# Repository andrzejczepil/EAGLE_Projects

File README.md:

# EAGLE_Projects
Schematics, footprints&amp;Boards

Projekt_KWP - a small project in collab with Agnieszka Zwolińska (UoT Gdańsk), project of working two-tone generator

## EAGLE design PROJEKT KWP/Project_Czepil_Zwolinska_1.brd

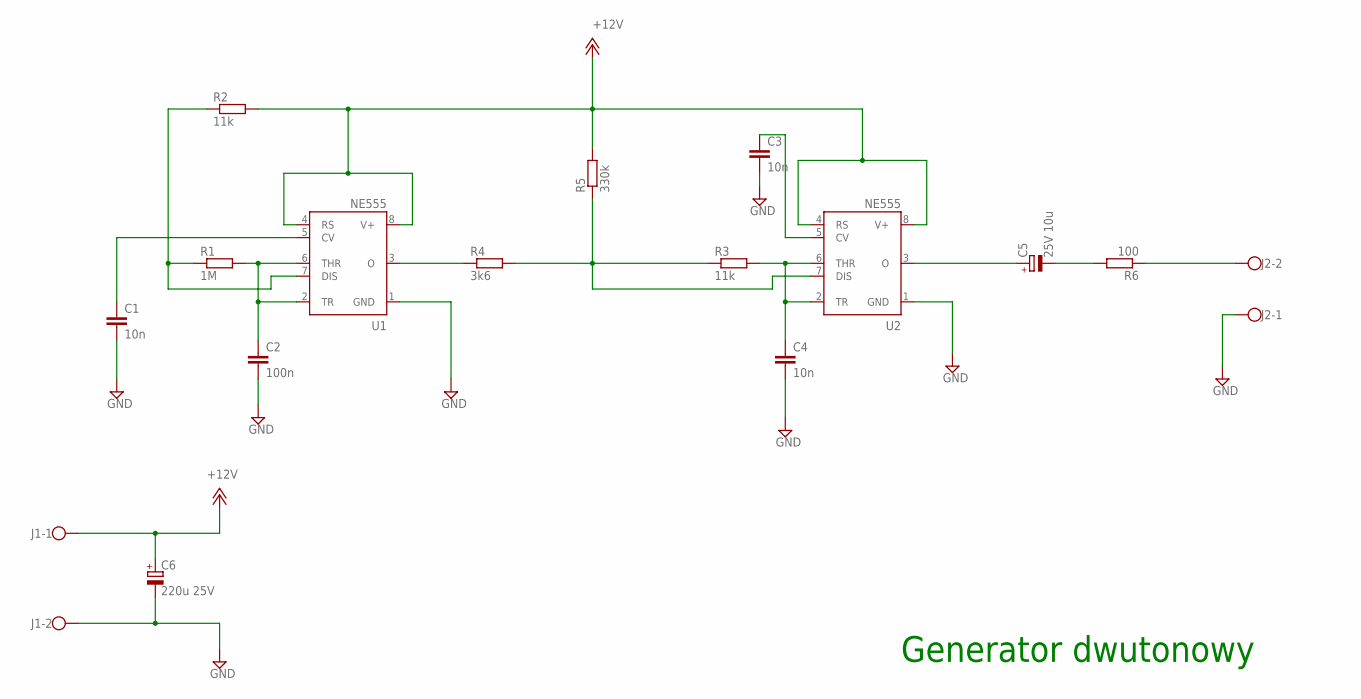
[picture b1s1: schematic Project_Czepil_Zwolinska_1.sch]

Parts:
C1, C3, C4: 10n; C1206
C2: 100n; C1206
C5: 25V 10u; E1,8-4
C6: 220u 25V; E2-4
J1, J2: W237-102
R1: 1M; 0207/10
R2, R3: 11k; 0207/10
R4: 3k6; 0207/10
R5: 330k; 0207/10
R6: 100; 0207/10
U1, U2: NE555; DIL-08

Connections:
+12V: C6.+, J1.1, R2.2, R5.2, U1.4 (RS), U1.8 (V+), U2.4 (RS), U2.8 (V+)
GND: C1.2, C2.2, C3.2, C4.2, C6.-, J1.2, J2.1, U1.1 (GND), U2.1 (GND)
unnamed: J2.2, R6.1
unnamed: C5.-, R6.2
unnamed: R3.1, R4.2, R5.1, U2.7 (DIS)
unnamed: C1.1, U1.5 (CV)
unnamed: R1.1, R2.1, U1.7 (DIS)
unnamed: C2.1, R1.2, U1.2 (TR), U1.6 (THR)
unnamed: C3.1, U2.5 (CV)
unnamed: C5.+, U2.3 (O)
unnamed: C4.1, R3.2, U2.2 (TR), U2.6 (THR)
unnamed: R4.1, U1.3 (O)

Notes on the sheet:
Generator dwutonowy

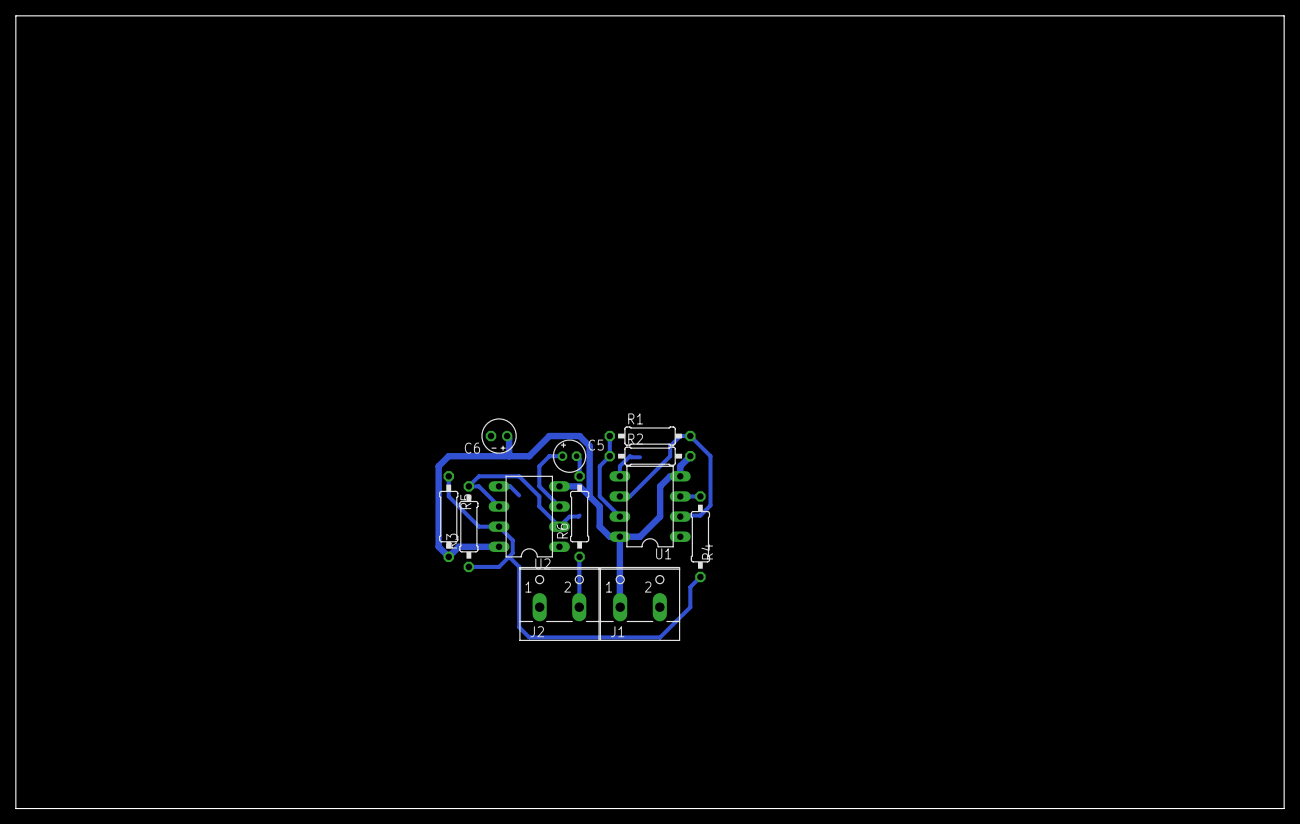
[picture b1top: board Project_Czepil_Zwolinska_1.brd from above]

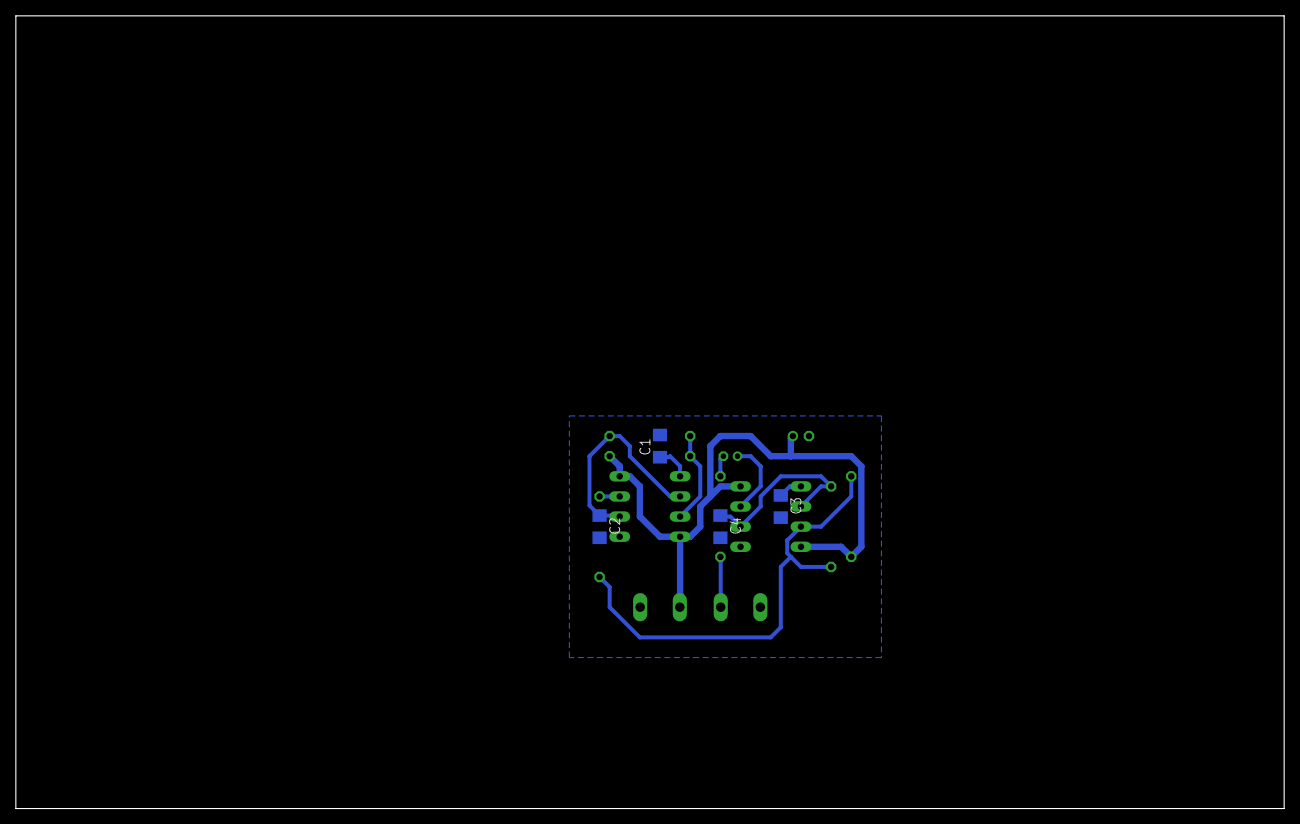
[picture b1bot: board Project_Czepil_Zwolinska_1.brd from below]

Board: 2 copper layers, 160.0 x 100.0 mm, 16 parts (4 on the bottom side), 12 nets.
